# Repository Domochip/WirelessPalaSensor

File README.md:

# WPalaSensor

This project aims to replace the Palazzetti (Fumis) room temperature sensor by an electronic simulator.  
It allows you to push home automation temperature to the stove.  
You can then keep native modulation that reduce power automatically when desired temperature is reached.  

## Compatibility

It appears that Fumis Controller is used by those brands for their stoves : 

* Palazzetti (All)
* Jotul
* TurboFonte
* Godin
* Fonte Flamme
* Invicta

If you have this controller in your stove, it's likely to be compatible.  

## Build your adapter

All files are inside `schematic` subfolder and has been designed with KiCad (free and open source)

### Schematic

### PCB

*We produced a small batch of this adapter for test/debugging and our personal use.
If you are interested, please PM.*

### Print your box

Box project (Fusion 360 & STL) can be found into `box` folder

### Code/Compile/Flash

Source code can be compiled using VisualStudioCode/Platformio and flashed onto a D1 Mini  
Or  
Download latest release in Release section

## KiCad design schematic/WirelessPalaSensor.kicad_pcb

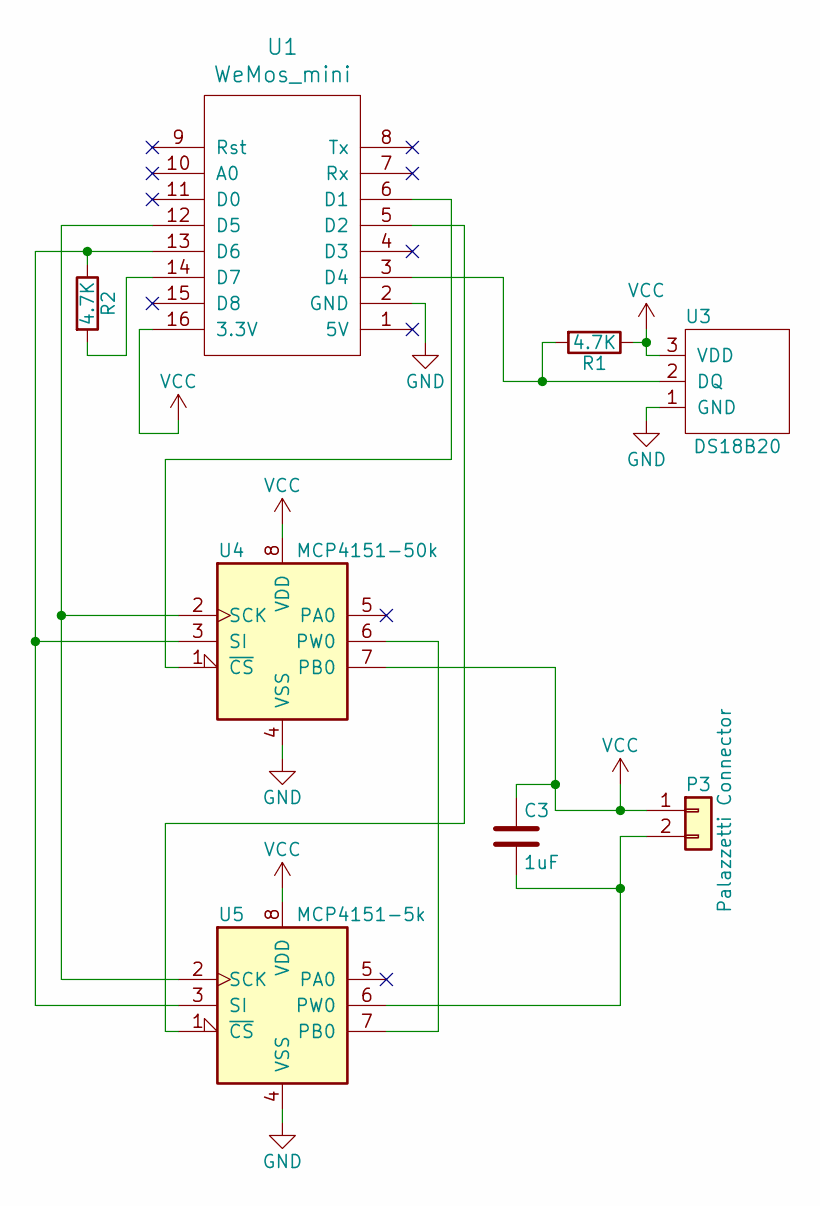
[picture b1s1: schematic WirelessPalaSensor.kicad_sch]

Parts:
C3: 1uF; C_0805_HandSoldering
P3: Palazzetti Connector; bornier2
R1, R2: 4.7K; R_0805_HandSoldering
U1: WeMos_mini; wemos-d1-mini-DIL-only
U3: DS18B20; Pin_Header_Straight_1x03_Pitch2.54mm
U4: MCP4151-50k; DIP-8_W7.62mm_LongPads
U5: MCP4151-5k; DIP-8_W7.62mm_LongPads

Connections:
GND: U1.2 (GND), U3.1 (GND), U4.4 (VSS), U5.4 (VSS)
unnamed: C3.2, P3.2, U5.6 (PW0)
unnamed: R1.2, U1.3 (D4), U3.2 (DQ)
unnamed: R2.1, U1.13 (D6), U4.3 (SI), U5.3 (SI)
unnamed: R2.2, U1.14 (D7)
unnamed: U1.5 (D2), U5.1 (~CS)
unnamed: U1.6 (D1), U4.1 (~CS)
unnamed: U1.12 (D5), U4.2 (SCK), U5.2 (SCK)
unnamed: U4.6 (PW0), U5.7 (PB0)
VCC: C3.1, P3.1, R1.1, U1.16 (3.3V), U3.3 (VDD), U4.7 (PB0), U4.8 (VDD), U5.8 (VDD)

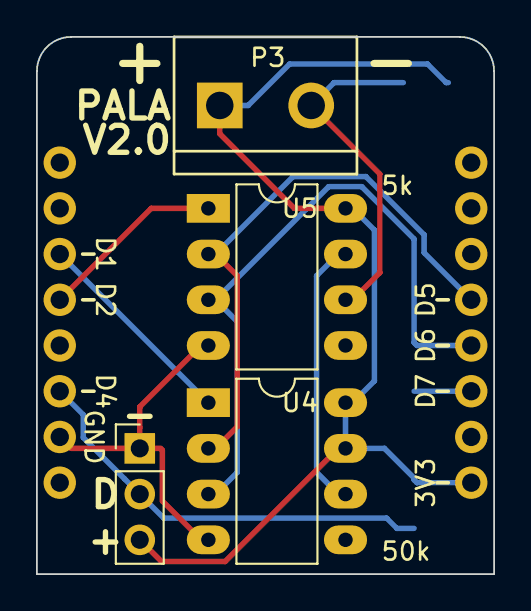
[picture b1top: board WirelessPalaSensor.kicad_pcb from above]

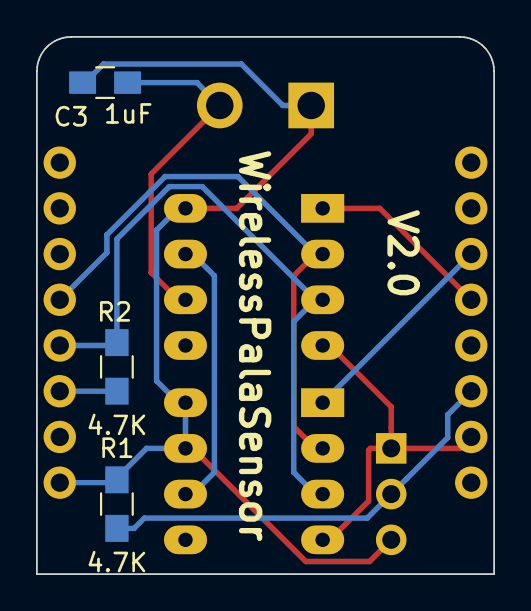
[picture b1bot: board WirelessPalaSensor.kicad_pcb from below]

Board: 2 copper layers, 25.4 x 29.8 mm, 8 parts (4 on the bottom side), 10 nets.

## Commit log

2018-03-13 V3.2.2 Initial Commit
2018-05-22 Switch to PlatformIO
2018-05-26 Add Base
2018-06-20 Switch to Base V1.0.10
2018-06-20 Add rename script to PlatformIO
2018-11-17 Switch to Base V1.1.6
    - No More PowerShell
    - GZIP and convertion to header done in python with platformIO
    - Webpages small improvement
2018-11-27 Fix base
2019-03-17 V3.2.3 Upgrade to Base V1.1.7
2019-03-30 V3.2.4 Update to base V1.2.1
2019-03-30 V3.2.5 Update CBox url
2019-03-31 V3.2.6 Update to base v1.2.2 Improve WiFi management
2019-04-01 V3.2.7 Use Ticker instead of SimpleTimer
2019-04-01 V3.2.8 use Ticker for flag and execute in loop
2019-04-02 Fix timing and Ticker init
2019-04-04 Bugfix
2019-04-06 Add library dependancies
2019-04-06 Fix Pure CSS - 1
2019-04-06 Fix Pure CSS - 2
2019-04-06 Fix lib dependencies
2019-04-07 PureCSS Fix because of GIT AutoCRLF Windows users enable autocrlf by default, and so pure-min.css crlf modified make bad integrity check
2019-04-07 Fix calibration web page
2019-06-01 Update Schematic to D1 Mini
2019-07-02 V3.3.0 Switch to D1 Mini
2019-07-02 New Box for D1 Mini based model
2019-08-12 Update gitignore
2019-10-13 Compatibility with Python3
2019-11-09 Up to Base V1.2.8
2019-11-16 Up to base V1.3.0
2019-11-17 Up to Base V1.3.1
2019-11-17 Base fix
2019-11-18 Up to Base V1.3.2
2019-11-22 Up to base V1.3.3
2019-11-23 Naming Convention
2020-01-11 Base Improvement LOG_SERIAL
2020-11-01 Increase query failure count
2020-11-01 Up to base V1.4.0 /!\ Configuration lost after flash /!\
2020-12-28 V3.3.5 Prepare MQTT implementation
2020-12-28 V3.3.6 make WiFiClient common
2020-12-28 put CBox request after ha request
2020-12-28 split WiFi.isConnected() condition
2020-12-31 RePrepare configuration structure
2020-12-31 Add refresh period and Max Failed Request in conf
2020-12-31 Add MQTT and split hostname
2020-12-31 V3.3.7 Implement MQTT
2020-12-31 V3.3.8 Adapt status page
2020-12-31 Improved Status
2020-12-31 MQTT and HTTPClient can't share WifiClient
2021-01-02 V3.4.0 MQTT ready
2021-11-30 Up to base V1.4.1
2021-12-04 Add README.md
2021-12-04 Update schematic
2023-12-14 Remove .vscode folder
2023-12-14 Ignore the whole .vscode folder
2023-12-14 Improved copy_base.py
2023-12-14 Improved prepare_webfiles.py
2023-12-17 WirelessBase update
2023-12-17 Replace AsyncWebServer by ESP8266WebServer
2023-12-17 new EventSource #define
2023-12-17 Format
2023-12-17 Remove Async libs
2023-12-26 Improve MQTT callback convertion
2023-12-26 handle MQTT payload containing JSON
2023-12-26 V4.0.0 Base Update and JSON payload for T1
2024-05-08 Fix build on !Windows
2024-05-08 change config form id to make it unique
2024-05-08 change calib form id to make it unique
2024-05-08 Stop CountDown if content has changed/reloaded
2024-05-14 Adapt code for ArduinoJson7
2024-09-03 Fix build on !Windows #2
2024-09-25 start platformio.ini factorization
2024-09-26 Adapt WebServer class name
2024-09-26 Make McpDigitalPot ESP32 compatible
2024-09-26 Adapt HTTPClient class
2024-09-26 Adapt Pins to ESP32 MiniKit
2024-09-26 Add ESP32 MiniKit to platformio.ini
2024-09-26 Adapt Ticker for ESP32
2024-09-26 Improve parseConfigJSON parsing
2024-09-26 Improve generateConfigJSON using JsonDocument
2024-09-26 Improve generateStatusJSON using JsonDocument
2024-09-26 Improve memory consumption before serializing
2024-09-28 Change parseConfigJSON signature
2024-09-28 Improve parseConfigJSON for compatibility
2024-09-28 Set default mqtt base topic to $model$
2024-09-28 Switch to JSON POST and reuse parseConfigJSON
2024-09-28 calibration page save button should send json too
2024-09-28 Calibration actions switch to json post
2024-09-28 V4.0.1 Base update + post switched to Json
2024-09-28 Add prepare release github action
2024-09-29 Remove tls fingerprint
2024-09-29 Remove fingerPrint
2024-09-29 Clean unused variable
2024-09-29 Factorize Jeedom and Fibaro code
2024-09-29 Improve platformio.ini
2024-09-29 Add Home Assistant MQTT autodiscovery
2024-09-29 Fix bad cboxIp in savefile
2024-09-29 V4.0.2 Fix + Home Assistant MQTT autodiscovery
2024-10-01 Update Base to 2.3.2 - Simplify Version number
2024-10-01 Simplify Version number sent to Home Assistant
2024-10-01 Adjust Github Action for new versioning
2024-10-01 Adapt code for Base 2.3.3
2024-10-01 Bump version to 4.0.3
2024-10-05 replace Max Failed Request with HA and Stove value timeout
2024-10-05 Rename some variables
2024-10-05 Add some MQTT publish for debug (DEV mode only)
2024-10-06 Implement TemperatureTimeout variables
2024-10-06 Fix incorrect config ids
2024-10-06 Improve core PalaSensor logic
2024-10-06 Avoid Delta calculation at the first Tick call
2024-10-06 Bump version to 4.0.4
2024-10-12 Adapt code for Base 2.3.7
2024-10-13 Add longLivedAccessToken variable and basic logic
2024-10-13 Add Home Assistant Entity ID variable
2024-10-13 Add Home Assistant http request code
2024-10-13 Move Jeedom apiKey to http secret
2024-10-13 Move Fibaro password to http secret
2024-10-13 Move Home Assistant long-lived access token to http secret
2024-10-16 Reduce mqtt username from 64 to 32 chars
2024-10-16 reduce mqtt password from 150 to 64 chars
2024-10-16 Reduce hassDiscoveryPrefix from 64 to 32 chars
2024-10-16 Reduce CBox T1 mqtt topic from 64 to 32 chars
2024-10-16 Adjust config webpage for Home Assistant HTTP
2024-10-16 Automatically add 8123 port only if tls is not checked
2024-10-16 Disable DEVELOPPER_MODE
2024-10-16 wording
2024-10-16 Add Home Assistant HTTP (#2)
    * Add longLivedAccessToken variable and basic logic
    * Add Home Assistant Entity ID variable
    * Add Home Assistant http request code
    * Move Jeedom apiKey to http secret
    * Move Fibaro password to http secret
    * Move Home Assistant long-lived access token to http secret
2024-10-16 Improve returned status text
2024-10-16 Improve Status texts
2024-10-16 Bump version to 4.0.5
2024-10-17 Add calibration div inside config.html
2024-10-17 Add inputs used for calibration
2024-10-17 Add getSteinhartHart function to config.html
2024-10-17 Add eventListeners for calibration buttons
2024-10-17 remove calib.html
2024-10-17 Improve calibButton eventListener code
2024-10-17 Move Calibration to Config webpage (#3)
    * Add calibration div inside config.html
    * Add inputs used for calibration
    * Add getSteinhartHart function to config.html
    * Add eventListeners for calibration buttons
    * remove calib.html
    * Improve calibButton eventListener code
2024-10-17 Bump version to 4.0.6
2024-10-19 Update schematic to KiCAD8
2024-10-19 Add KiCad gitignore
2024-10-19 Adapt for Base 2.3.9
2024-10-20 Send module infos to MQTT baseTopic
2024-10-20 Use _appName for MQTT status reporting
2024-10-20 Improve Home Automation status
2024-10-20 Complete WPalaSensor status improvment
2024-10-20 Optimization
2024-10-21 Bump version to 4.0.7
2024-10-21 Rename WebPalaSensor class to WPalaSensor
2024-10-21 Rename files from WirelessPalaSensor to WPalaSensor
2024-10-21 Change appName in webpage
2024-10-21 Change firmware file name
2024-10-21 Adapt code for Base 2.3.11
2024-10-21 Update copy_base.py script
